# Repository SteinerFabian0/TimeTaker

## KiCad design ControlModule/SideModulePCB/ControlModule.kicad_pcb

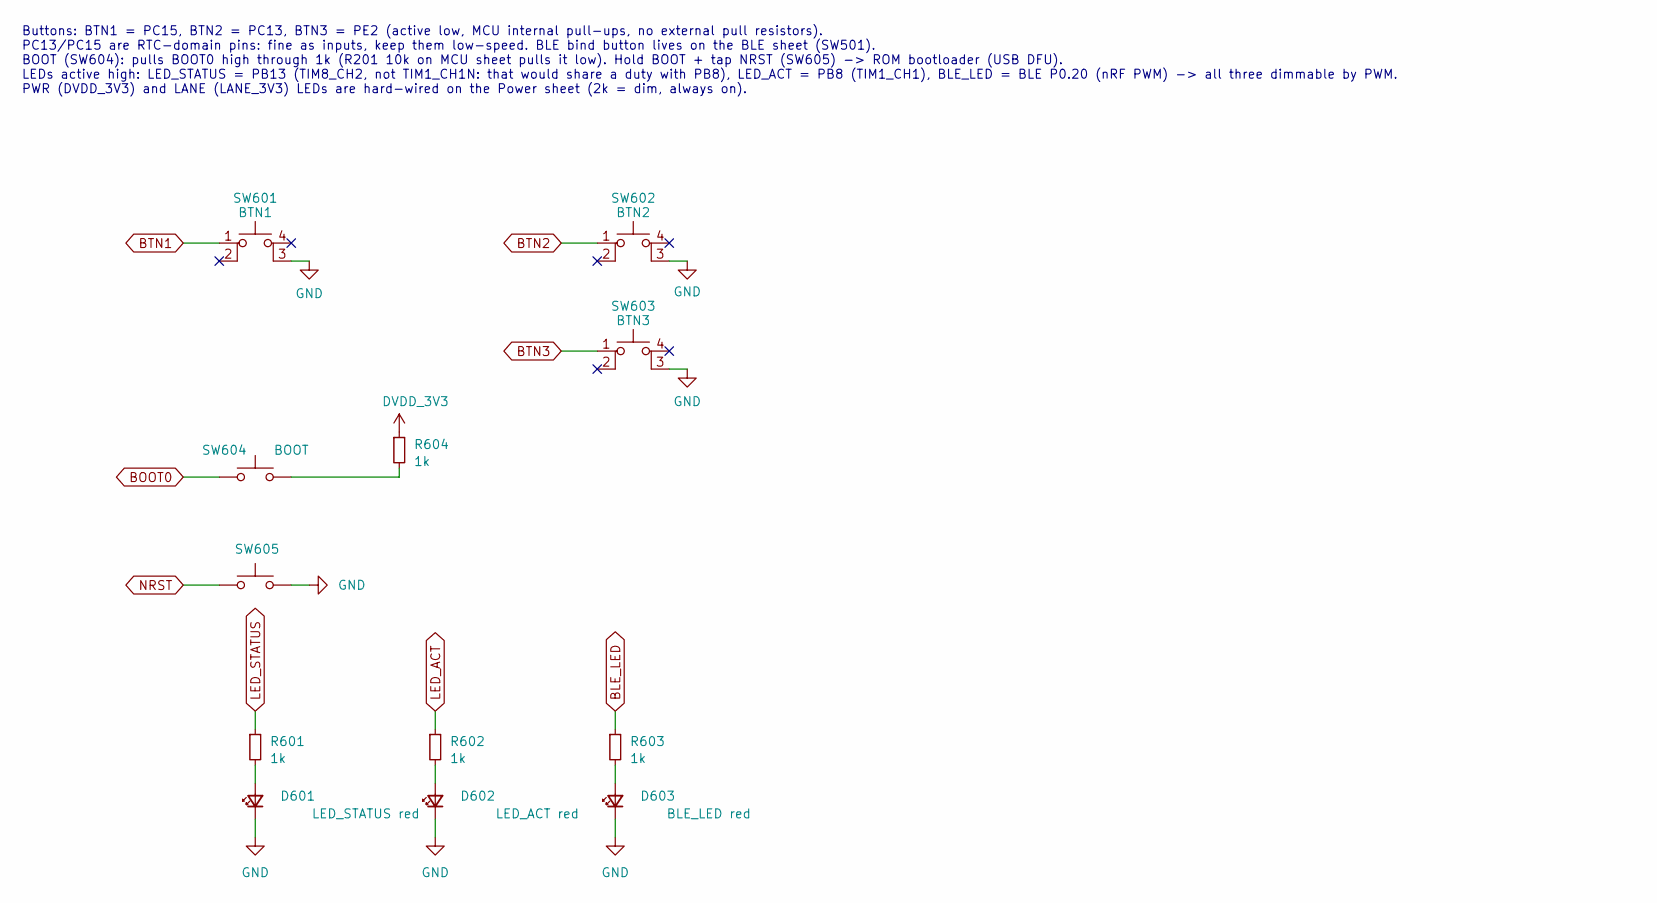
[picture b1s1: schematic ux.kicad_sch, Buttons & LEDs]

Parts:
D601: LED_STATUS red; LED_D5.0mm
D602: LED_ACT red; LED_D5.0mm
D603: BLE_LED red; LED_D5.0mm
R601, R602, R603, R604: 1k; R_0603_1608Metric
SW601: BTN1; Switch_Tactile_Smd_Gullwing
SW602: BTN2; Switch_Tactile_Smd_Gullwing
SW603: BTN3; Switch_Tactile_Smd_Gullwing
SW604: BOOT; SW_SPST_TS-1088-xR025; MPN TS-1088-AR02016; LCSC C720477
SW605: NRST; SW_SPST_TS-1088-xR025; MPN TS-1088-AR02016; LCSC C720477

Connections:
BLE_LED: R603.1; also elsewhere on the board
BOOT0: SW604.1; also elsewhere on the board
BTN1: SW601.1; also elsewhere on the board
BTN2: SW602.1; also elsewhere on the board
BTN3: SW603.1; also elsewhere on the board
DVDD_3V3: R604.1; also elsewhere on the board
GND: D601.1 (K), D602.1 (K), D603.1 (K), SW601.3 (K), SW602.3 (K), SW603.3 (K), SW605.2; also elsewhere on the board
LED_ACT: R602.1; also elsewhere on the board
LED_STATUS: R601.1; also elsewhere on the board
NRST: SW605.1; also elsewhere on the board
unnamed: D601.2 (A), R601.2
unnamed: D602.2 (A), R602.2
unnamed: D603.2 (A), R603.2
unnamed: R604.2, SW604.2

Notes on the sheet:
Buttons: BTN1 = PC15, BTN2 = PC13, BTN3 = PE2 (active low, MCU internal pull-ups, no external pull resistors). PC13/PC15 are RTC-domain pins: fine as inputs, keep them low-speed. BLE bind button lives on the BLE sheet (SW501). BOOT (SW604): pulls BOOT0 high through 1k (R201 10k on MCU sheet pulls i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

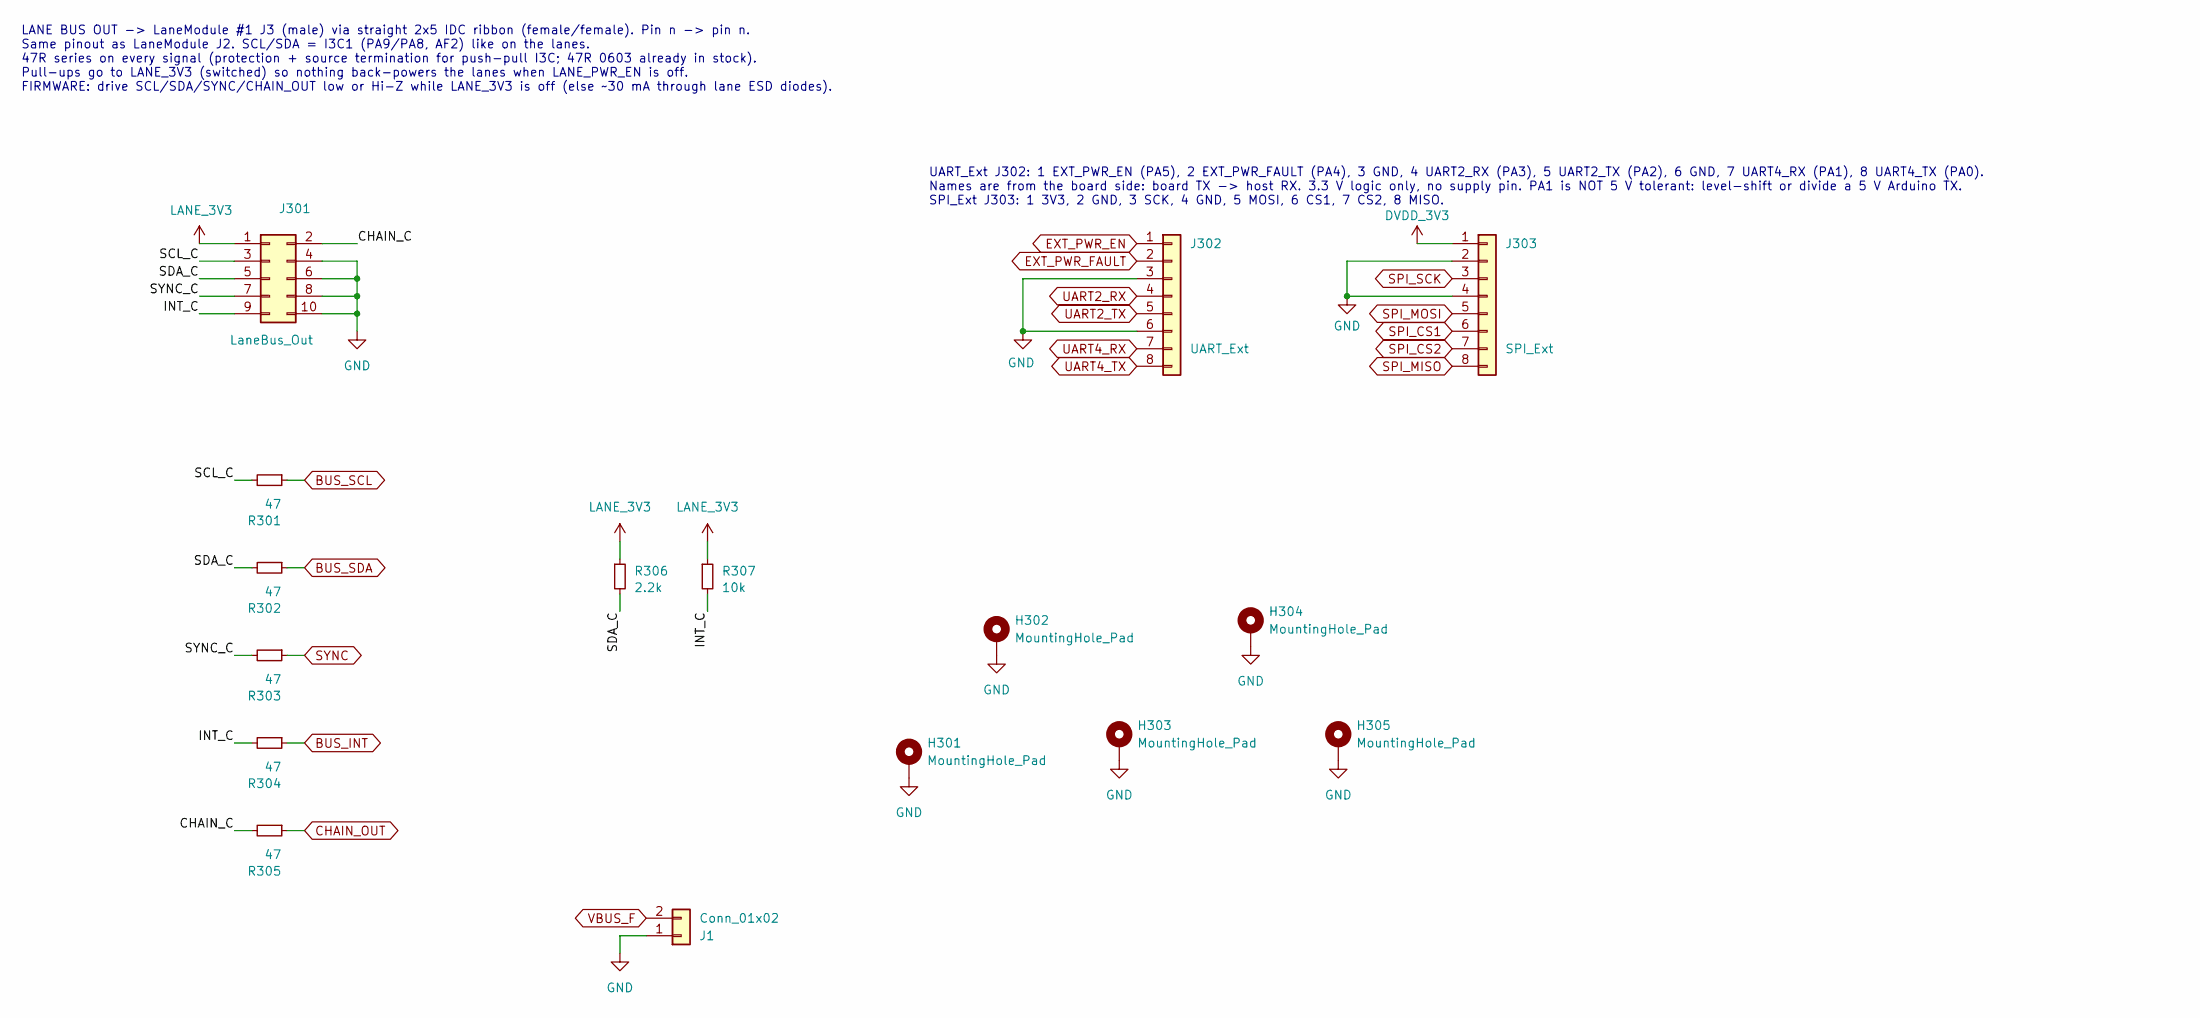
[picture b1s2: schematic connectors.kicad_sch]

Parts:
H301: MountingHole_Pad; MountingHole_3.2mm_M3_DIN965_Pad
H302, H303, H304, H305: MountingHole_Pad; MountingHole_2.5mm_Pad
J1: Conn_01x02; PinHeader_1x02_P2.54mm_Vertical
J301: LaneBus_Out; PinHeader_2x05_P2.54mm_Vertical
J302: UART_Ext; PinHeader_1x08_P2.54mm_Vertical
J303: SPI_Ext; PinHeader_1x08_P2.54mm_Vertical
R301, R302, R303, R304, R305: 47; R_0603_1608Metric; MPN 0603WAF470JT5E; LCSC C23182
R306: 2.2k; R_0603_1608Metric
R307: 10k; R_0603_1608Metric

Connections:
/Connectors/CHAIN_C: J301.2, R305.2
/Connectors/INT_C: J301.9, R304.2, R307.2
/Connectors/SCL_C: J301.3, R301.2
/Connectors/SDA_C: J301.5, R302.2, R306.2
/Connectors/SYNC_C: J301.7, R303.2
BUS_INT: R304.1; also elsewhere on the board
BUS_SCL: R301.1; also elsewhere on the board
BUS_SDA: R302.1; also elsewhere on the board
CHAIN_OUT: R305.1; also elsewhere on the board
DVDD_3V3: J303.1; also elsewhere on the board
EXT_PWR_EN: J302.1; also elsewhere on the board
EXT_PWR_FAULT: J302.2; also elsewhere on the board
GND: H301.1 (1_1), H302.1 (1_1), H303.1 (1_1), H304.1 (1_1), H305.1 (1_1), J1.1, J301.4, J301.6, J301.8, J301.10, J302.3, J302.6, J303.2, J303.4; also elsewhere on the board
LANE_3V3: J301.1, R306.1, R307.1; also elsewhere on the board
SPI_CS1: J303.6; also elsewhere on the board
SPI_CS2: J303.7; also elsewhere on the board
SPI_MISO: J303.8; also elsewhere on the board
SPI_MOSI: J303.5; also elsewhere on the board
SPI_SCK: J303.3; also elsewhere on the board
SYNC: R303.1; also elsewhere on the board
UART2_RX: J302.4; also elsewhere on the board
UART2_TX: J302.5; also elsewhere on the board
UART4_RX: J302.7; also elsewhere on the board
UART4_TX: J302.8; also elsewhere on the board
VBUS_F: J1.2; also elsewhere on the board

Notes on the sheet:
LANE BUS OUT -> LaneModule #1 J3 (male) via straight 2x5 IDC ribbon (female/female). Pin n -> pin n. Same pinout as LaneModule J2. SCL/SDA = I3C1 (PA9/PA8, AF2) like on the lanes. 47R series on every signal (protection + source termination for push-pull I3C; 47R 0603 already in stock). Pull-ups go 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
UART_Ext J302: 1 EXT_PWR_EN (PA5), 2 EXT_PWR_FAULT (PA4), 3 GND, 4 UART2_RX (PA3), 5 UART2_TX (PA2), 6 GND, 7 UART4_RX (PA1), 8 UART4_TX (PA0). Names are from the board side: board TX -> host RX. 3.3 V logic only, no supply pin. PA1 is NOT 5 V tolerant: level-shift or divide a 5 V Arduino TX. SPI_E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

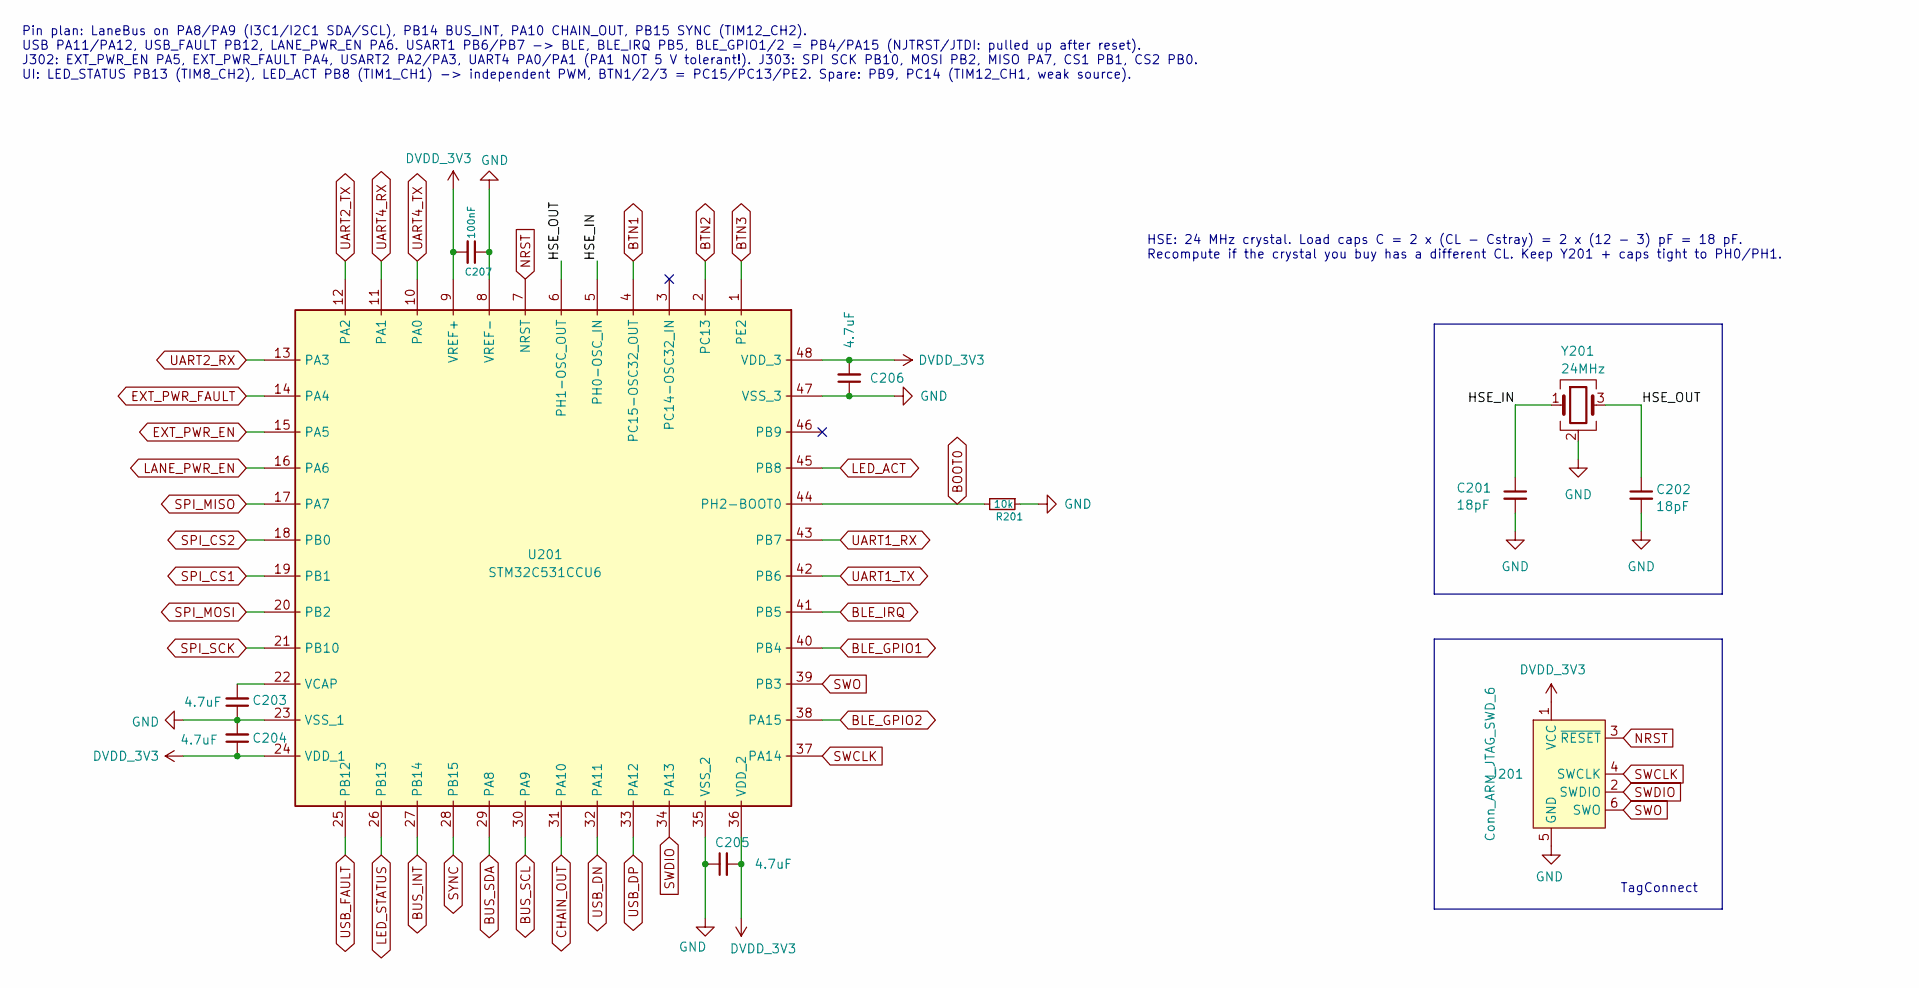
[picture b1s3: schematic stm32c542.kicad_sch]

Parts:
C201, C202: 18pF; C_0402_1005Metric
C203, C204, C205, C206: 4.7uF; C_0402_1005Metric; MPN CL05A475MP5NRNC; LCSC C23733
C207: 100nF; C_0402_1005Metric; MPN CL05B104KO5NNNC; LCSC C1525
J201: Conn_ARM_JTAG_SWD_6; Tag-Connect_TC2030-IDC-NL_2x03_P1.27mm_Vertical
R201: 10k; R_0603_1608Metric
U201: STM32C531CCU6; QFN50P700X700X60-49N-D; Manufacturer_Part_Number STM32C531CCU6
Y201: 24MHz; Crystal_SMD_3225-4Pin_3.2x2.5mm

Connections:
/STM32C5/HSE_IN: C201.1, U201.5 (PH0-OSC_IN), Y201.1
/STM32C5/HSE_OUT: C202.1, U201.6 (PH1-OSC_OUT), Y201.3
BLE_GPIO1: U201.40 (PB4); also elsewhere on the board
BLE_GPIO2: U201.38 (PA15); also elsewhere on the board
BLE_IRQ: U201.41 (PB5); also elsewhere on the board
BOOT0: R201.2, U201.44 (PH2-BOOT0); also elsewhere on the board
BTN1: U201.4 (PC15-OSC32_OUT); also elsewhere on the board
BTN2: U201.2 (PC13); also elsewhere on the board
BTN3: U201.1 (PE2); also elsewhere on the board
BUS_INT: U201.27 (PB14); also elsewhere on the board
BUS_SCL: U201.30 (PA9); also elsewhere on the board
BUS_SDA: U201.29 (PA8); also elsewhere on the board
CHAIN_OUT: U201.31 (PA10); also elsewhere on the board
DVDD_3V3: C204.1, C205.2, C206.2, C207.2, J201.1 (VCC), U201.9 (VREF+), U201.24 (VDD_1), U201.36 (VDD_2), U201.48 (VDD_3); also elsewhere on the board
EXT_PWR_EN: U201.15 (PA5); also elsewhere on the board
EXT_PWR_FAULT: U201.14 (PA4); also elsewhere on the board
GND: C201.2, C202.2, C203.1, C204.2, C205.1, C206.1, C207.1, J201.5 (GND), R201.1, U201.8 (VREF-), U201.23 (VSS_1), U201.35 (VSS_2), U201.47 (VSS_3), U201.49 (VSS_4), Y201.2 (G), Y201.4 (G); also elsewhere on the board
LANE_PWR_EN: U201.16 (PA6); also elsewhere on the board
LED_ACT: U201.45 (PB8); also elsewhere on the board
LED_STATUS: U201.26 (PB13); also elsewhere on the board
NRST: J201.3 (~RESET), U201.7 (NRST); also elsewhere on the board
unnamed: C203.2, U201.22 (VCAP)
SPI_CS1: U201.19 (PB1); also elsewhere on the board
SPI_CS2: U201.18 (PB0); also elsewhere on the board
SPI_MISO: U201.17 (PA7); also elsewhere on the board
SPI_MOSI: U201.20 (PB2); also elsewhere on the board
SPI_SCK: U201.21 (PB10); also elsewhere on the board
SWCLK: J201.4 (SWCLK), U201.37 (PA14)
SWDIO: J201.2 (SWDIO), U201.34 (PA13)
SWO: J201.6 (SWO), U201.39 (PB3)
SYNC: U201.28 (PB15); also elsewhere on the board
UART1_RX: U201.43 (PB7); also elsewhere on the board
UART1_TX: U201.42 (PB6); also elsewhere on the board
UART2_RX: U201.13 (PA3); also elsewhere on the board
UART2_TX: U201.12 (PA2); also elsewhere on the board
UART4_RX: U201.11 (PA1); also elsewhere on the board
UART4_TX: U201.10 (PA0); also elsewhere on the board
USB_DN: U201.32 (PA11); also elsewhere on the board
USB_DP: U201.33 (PA12); also elsewhere on the board
USB_FAULT: U201.25 (PB12); also elsewhere on the board

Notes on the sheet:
HSE: 24 MHz crystal. Load caps C = 2 x (CL - Cstray) = 2 x (12 - 3) pF = 18 pF. Recompute if the crystal you buy has a different CL. Keep Y201 + caps tight to PH0/PH1.
Pin plan: LaneBus on PA8/PA9 (I3C1/I2C1 SDA/SCL), PB14 BUS_INT, PA10 CHAIN_OUT, PB15 SYNC (TIM12_CH2). USB PA11/PA12, USB_FAULT PB12, LANE_PWR_EN PA6. USART1 PB6/PB7 -> BLE, BLE_IRQ PB5, BLE_GPIO1/2 = PB4/PA15 (NJTRST/JTDI: pulled up after reset). J302: EXT_PWR_EN PA5, EXT_PWR_FAULT PA4, USART2 PA2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
TagConnect

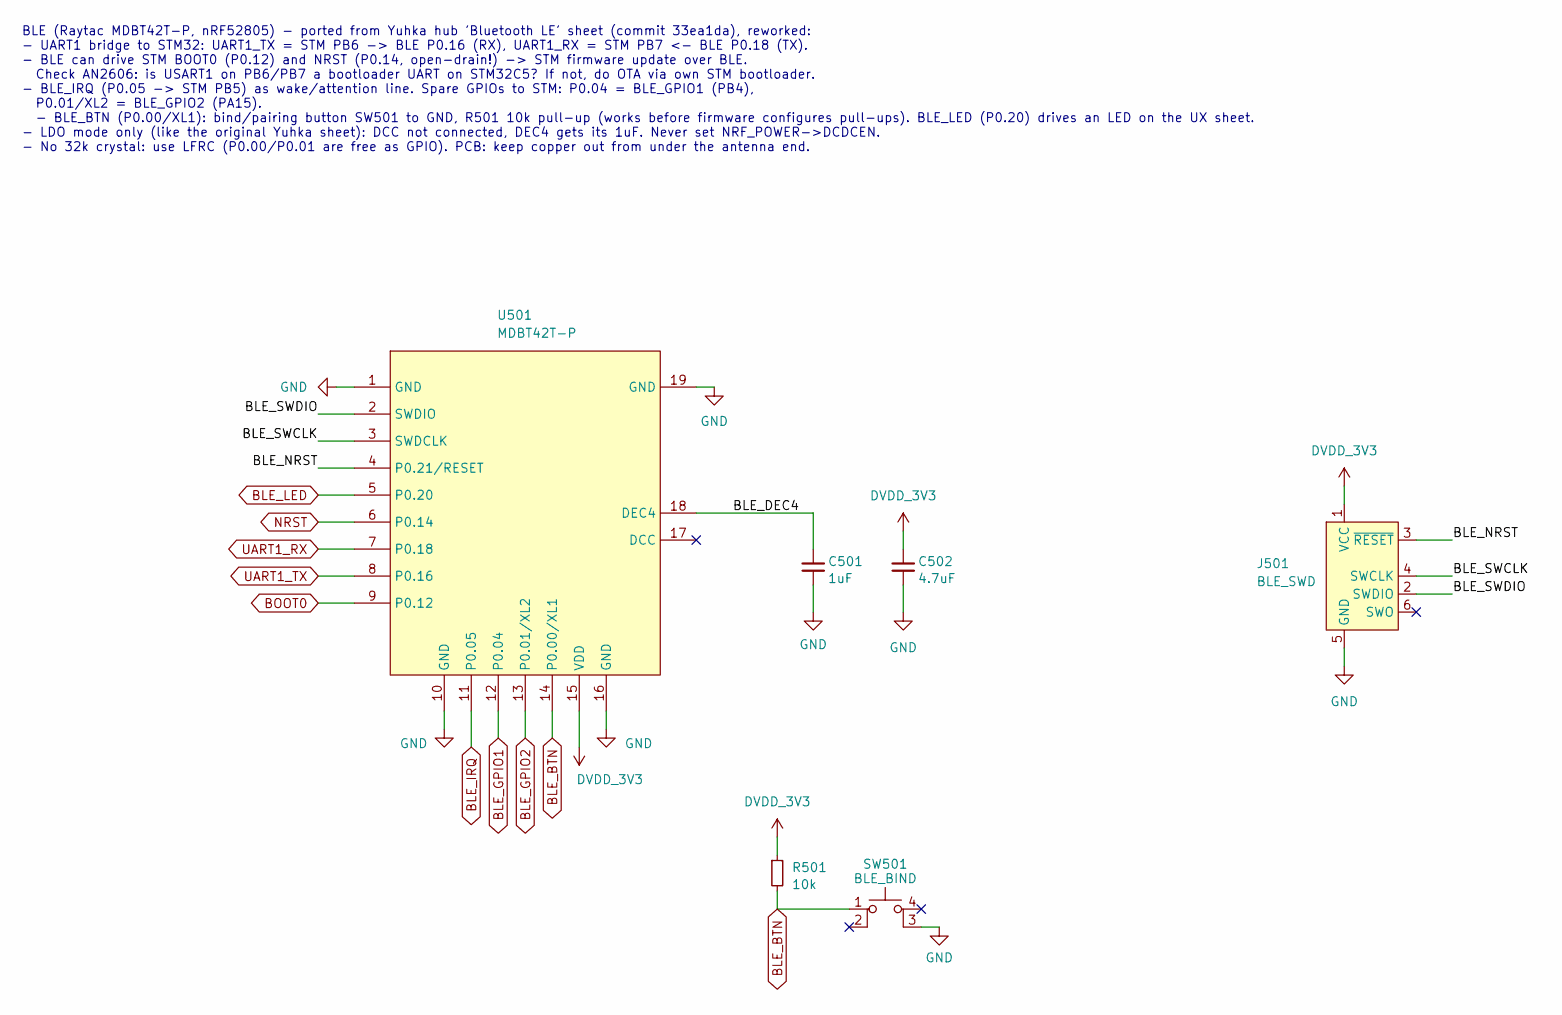
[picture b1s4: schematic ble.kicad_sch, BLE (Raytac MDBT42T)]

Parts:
C501: 1uF; C_0402_1005Metric
C502: 4.7uF; C_0402_1005Metric; MPN CL05A475MP5NRNC; LCSC C23733
J501: BLE_SWD; Tag-Connect_TC2030-IDC-NL_2x03_P1.27mm_Vertical
R501: 10k; R_0603_1608Metric
SW501: BLE_BIND; Switch_Tactile_Smd_Gullwing
U501: MDBT42T-P; MDBT42T

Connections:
/BLE/BLE_DEC4: C501.1, U501.18 (DEC4)
/BLE/BLE_NRST: J501.3 (~RESET), U501.4 (P0.21/RESET)
/BLE/BLE_SWCLK: J501.4 (SWCLK), U501.3 (SWDCLK)
/BLE/BLE_SWDIO: J501.2 (SWDIO), U501.2 (SWDIO)
BLE_BTN: R501.2, SW501.1, U501.14 (P0.00/XL1)
BLE_GPIO1: U501.12 (P0.04); also elsewhere on the board
BLE_GPIO2: U501.13 (P0.01/XL2); also elsewhere on the board
BLE_IRQ: U501.11 (P0.05); also elsewhere on the board
BLE_LED: U501.5 (P0.20); also elsewhere on the board
BOOT0: U501.9 (P0.12); also elsewhere on the board
DVDD_3V3: C502.1, J501.1 (VCC), R501.1, U501.15 (VDD); also elsewhere on the board
GND: C501.2, C502.2, J501.5 (GND), SW501.3 (K), U501.1 (GND), U501.10 (GND), U501.16 (GND), U501.19 (GND); also elsewhere on the board
NRST: U501.6 (P0.14); also elsewhere on the board
UART1_RX: U501.7 (P0.18); also elsewhere on the board
UART1_TX: U501.8 (P0.16); also elsewhere on the board

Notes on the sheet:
BLE (Raytac MDBT42T-P, nRF52805) - ported from Yuhka hub 'Bluetooth LE' sheet (commit 33ea1da), reworked: - UART1 bridge to STM32: UART1_TX = STM PB6 -> BLE P0.16 (RX), UART1_RX = STM PB7 <- BLE P0.18 (TX). - BLE can drive STM BOOT0 (P0.12) and NRST (P0.14, open-drain!) -> STM firmware update over 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

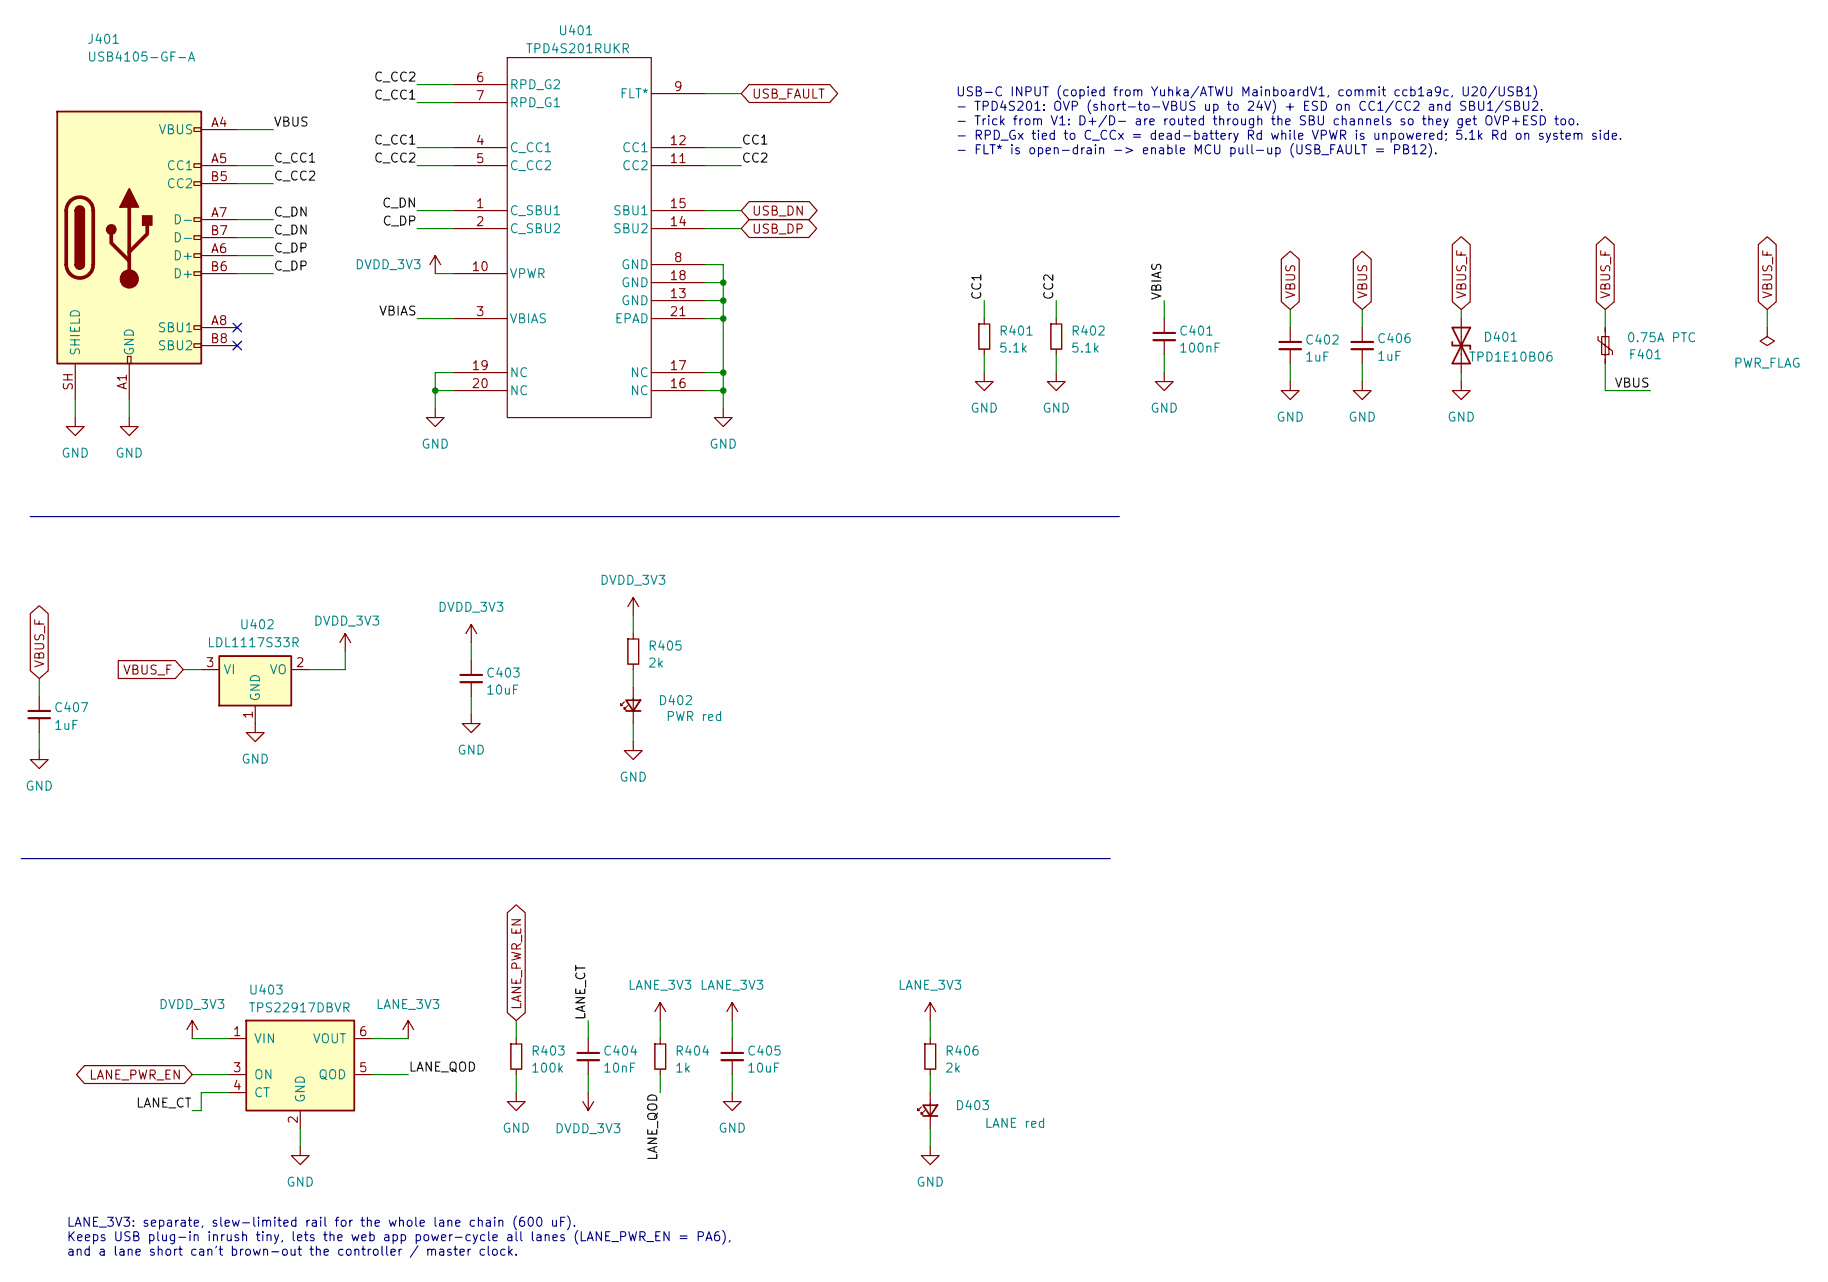
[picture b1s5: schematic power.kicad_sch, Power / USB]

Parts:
C401: 100nF; C_0402_1005Metric; MPN CL05B104KO5NNNC; LCSC C1525
C402, C406, C407: 1uF; C_0603_1608Metric; Voltage 50V; MPN CL10A105KB8NNNC; LCSC C15849
C403, C405: 10uF; C_0603_1608Metric; MPN CL10A106KP8NNNC; LCSC C19702
C404: 10nF; C_0402_1005Metric
D401: TPD1E10B06; Texas_DPY0002A_0.6x1mm_P0.65mm; MPN TPD1E10B06DPYR; LCSC C1847652
D402: PWR red; LED_D5.0mm
D403: LANE red; LED_D5.0mm
F401: 0.75A PTC; Fuse_1206_3216Metric; MPN 1206L075THYR
J401: USB4105-GF-A; USB_C_Receptacle_GCT_USB4105-xx-A_16P_TopMnt_Horizontal
R401, R402: 5.1k; R_0402_1005Metric
R403: 100k; R_0603_1608Metric
R404: 1k; R_0603_1608Metric
R405, R406: 2k; R_0603_1608Metric
U401: TPD4S201RUKR; QFN_TPD4S201RUKR_TEX
U402: LDL1117S33R; SOT-223-3_TabPin2
U403: TPS22917DBVR; SOT-23-6

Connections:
/Power/CC1: R401.1, U401.12 (CC1)
/Power/CC2: R402.1, U401.11 (CC2)
/Power/C_CC1: J401.A5 (CC1), U401.4 (C_CC1), U401.7 (RPD_G1)
/Power/C_CC2: J401.B5 (CC2), U401.5 (C_CC2), U401.6 (RPD_G2)
/Power/C_DN: J401.A7 (D-), J401.B7 (D-), U401.1 (C_SBU1)
/Power/C_DP: J401.A6 (D+), J401.B6 (D+), U401.2 (C_SBU2)
/Power/LANE_CT: C404.1, U403.4 (CT)
/Power/LANE_QOD: R404.2, U403.5 (QOD)
/Power/VBIAS: C401.1, U401.3 (VBIAS)
DVDD_3V3: C403.1, C404.2, R405.1, U401.10 (VPWR), U402.2 (VO), U403.1 (VIN); also elsewhere on the board
GND: C401.2, C402.2, C403.2, C405.2, C406.2, C407.2, D401.2 (A2), D402.1 (K), D403.1 (K), J401.A1 (GND), J401.A12 (GND), J401.B1 (GND), J401.B12 (GND), J401.SH (SHIELD), R401.2, R402.2, R403.2, U401.8 (GND), U401.13 (GND), U401.16 (NC), U401.17 (NC), U401.18 (GND), U401.19 (NC), U401.20 (NC), U401.21 (EPAD), U402.1 (GND), U403.2 (GND); also elsewhere on the board
LANE_3V3: C405.1, R404.1, R406.1, U403.6 (VOUT); also elsewhere on the board
LANE_PWR_EN: R403.1, U403.3 (ON); also elsewhere on the board
unnamed: D402.2 (A), R405.2
unnamed: D403.2 (A), R406.2
USB_DN: U401.15 (SBU1); also elsewhere on the board
USB_DP: U401.14 (SBU2); also elsewhere on the board
USB_FAULT: U401.9 (FLT*); also elsewhere on the board
VBUS: C402.1, C406.1, F401.1, J401.A4 (VBUS), J401.A9 (VBUS), J401.B4 (VBUS), J401.B9 (VBUS)
VBUS_F: C407.1, D401.1 (A1), F401.2, U402.3 (VI); also elsewhere on the board

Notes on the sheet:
USB-C INPUT (copied from Yuhka/ATWU MainboardV1, commit ccb1a9c, U20/USB1) - TPD4S201: OVP (short-to-VBUS up to 24V) + ESD on CC1/CC2 and SBU1/SBU2. - Trick from V1: D+/D- are routed through the SBU channels so they get OVP+ESD too. - RPD_Gx tied to C_CCx = dead-battery Rd while VPWR is unpowered; 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
LANE_3V3: separate, slew-limited rail for the whole lane chain (600 uF). Keeps USB plug-in inrush tiny, lets the web app power-cycle all lanes (LANE_PWR_EN = PA6), and a lane short can't brown-out the controller / master clock.

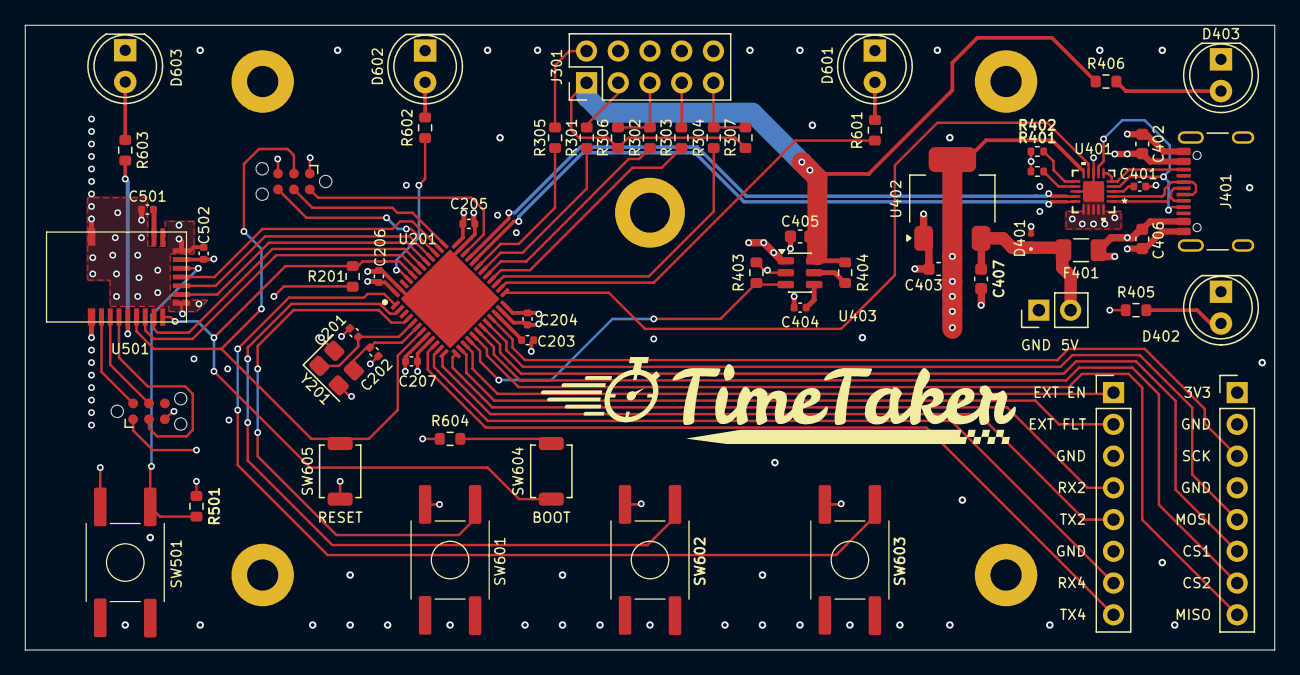
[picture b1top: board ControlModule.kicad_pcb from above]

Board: 4 copper layers, 100.0 x 50.0 mm, 66 parts (0 on the bottom side), 69 nets.

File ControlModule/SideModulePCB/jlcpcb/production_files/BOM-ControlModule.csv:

Comment,Designator,Footprint,LCSC,Quantity
100nF,"C207,C401",C_0402_1005Metric,C1525,2
10uF,"C403,C405",C_0603_1608Metric,C19702,2
1uF,"C402,C406,C407",C_0603_1608Metric,C15849,3
4.7uF,"C203,C204,C205,C206,C502",C_0402_1005Metric,C23733,5
47,"R301,R302,R303,R304,R305",R_0603_1608Metric,C23182,5
BOOT,SW604,SW_SPST_TS-1088-xR025,C720477,1
NRST,SW605,SW_SPST_TS-1088-xR025,C720477,1
TPD1E10B06,D401,Texas_DPY0002A_0.6x1mm_P0.65mm,C1847652,1
24MHz,Y201,Crystal_SMD_3225-4Pin_3.2x2.5mm,,1
PWR red,D402,LED_D5.0mm,,1
BTN2,SW602,Switch_Tactile_Smd_Gullwing,,1
LaneBus_Out,J301,PinHeader_2x05_P2.54mm_Vertical,,1
2k,R405,R_0603_1608Metric,,1
TPD4S201RUKR,U401,QFN_TPD4S201RUKR_TEX,,1
1k,R603,R_0603_1608Metric,,1
Conn_01x02,J1,PinHeader_1x02_P2.54mm_Vertical,,1
USB4105-GF-A,J401,USB_C_Receptacle_GCT_USB4105-xx-A_16P_TopMnt_Horizontal,,1
BTN1,SW601,Switch_Tactile_Smd_Gullwing,,1
LED_ACT red,D602,LED_D5.0mm,,1
STM32C531CCU6,U201,QFN50P700X700X60-49N-D,,1
TPS22917DBVR,U403,SOT-23-6,,1
SPI_Ext,J303,PinHeader_1x08_P2.54mm_Vertical,,1
1k,R601,R_0603_1608Metric,,1
1uF,C501,C_0402_1005Metric,,1
1k,R602,R_0603_1608Metric,,1
MDBT42T-P,U501,MDBT42T,,1
LANE red,D403,LED_D5.0mm,,1
BLE_SWD,J501,Tag-Connect_TC2030-IDC-NL_2x03_P1.27mm_Vertical,,1
0.75A PTC,F401,Fuse_1206_3216Metric,,1
2.2k,R306,R_0603_1608Metric,,1
18pF,C202,C_0402_1005Metric,,1
UART_Ext,J302,PinHeader_1x08_P2.54mm_Vertical,,1
LDL1117S33R,U402,SOT-223-3_TabPin2,,1
100k,R403,R_0603_1608Metric,,1
BTN3,SW603,Switch_Tactile_Smd_Gullwing,,1
18pF,C201,C_0402_1005Metric,,1
2k,R406,R_0603_1608Metric,,1
1k,R604,R_0603_1608Metric,,1
10nF,C404,C_0402_1005Metric,,1
BLE_LED red,D603,LED_D5.0mm,,1
BLE_BIND,SW501,Switch_Tactile_Smd_Gullwing,,1
10k,R307,R_0603_1608Metric,,1
5.1k,R401,R_0402_1005Metric,,1
5.1k,R402,R_0402_1005Metric,,1
1k,R404,R_0603_1608Metric,,1
10k,R201,R_0603_1608Metric,,1
10k,R501,R_0603_1608Metric,,1
LED_STATUS red,D601,LED_D5.0mm,,1

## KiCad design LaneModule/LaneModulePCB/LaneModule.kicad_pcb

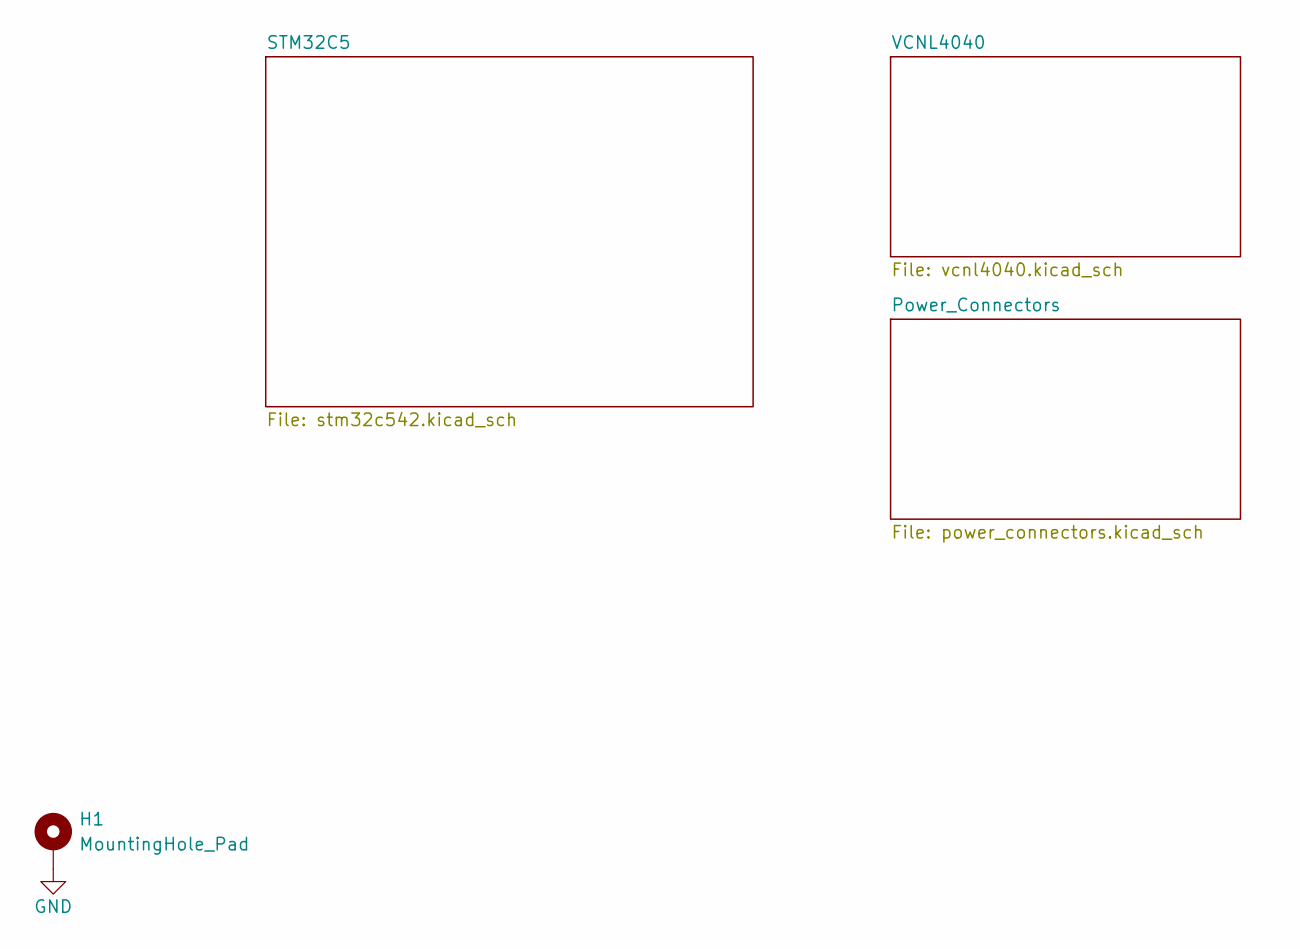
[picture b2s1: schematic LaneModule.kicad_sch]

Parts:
H1: MountingHole_Pad; MountingHole_2.5mm_Pad

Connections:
GND: H1.1 (1_1); also elsewhere on the board

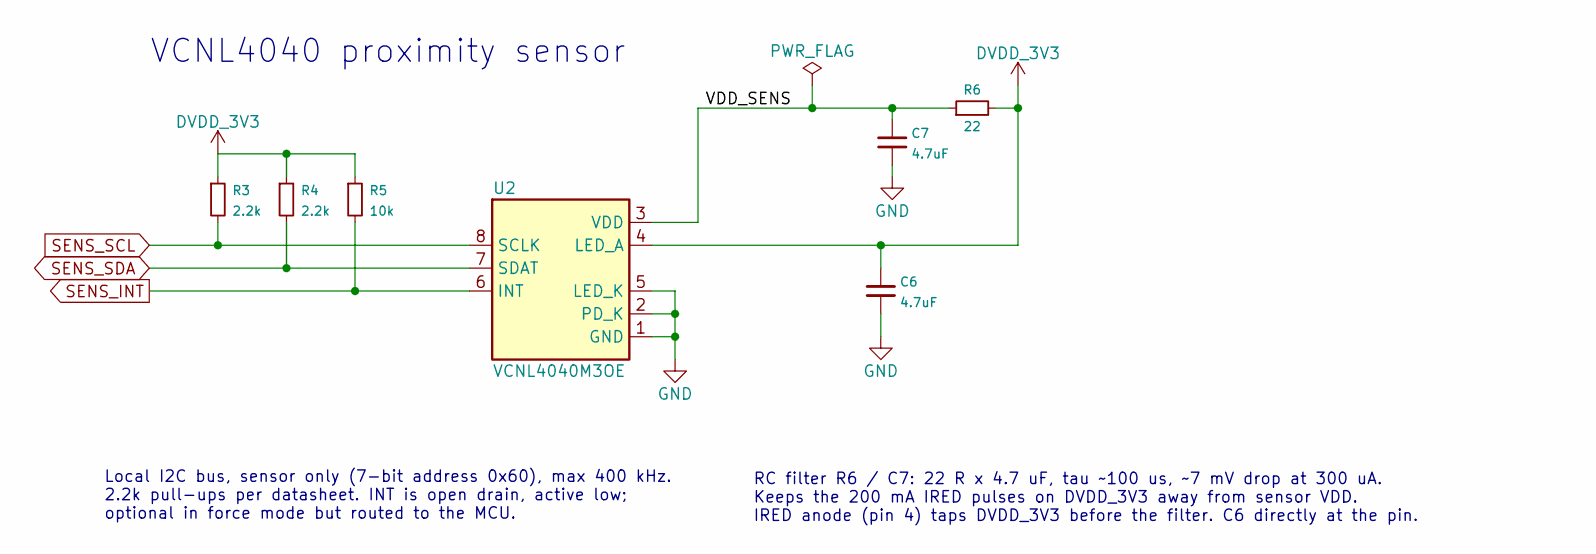
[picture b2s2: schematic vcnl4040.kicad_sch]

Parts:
C6, C7: 4.7uF; C_0402_1005Metric; MPN CL05A475MP5NRNC; LCSC C23733
R3, R4: 2.2k; R_0603_1608Metric
R5: 10k; R_0603_1608Metric
R6: 22; R_0603_1608Metric
U2: VCNL4040M3OE; MPN VCNL4040M3OE; LCSC C142526

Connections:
/VCNL4040/VDD_SENS: C7.1, R6.1, U2.3 (VDD)
DVDD_3V3: C6.1, R3.1, R4.1, R5.1, R6.2, U2.4 (LED_A); also elsewhere on the board
GND: C6.2, C7.2, U2.1 (GND), U2.2 (PD_K), U2.5 (LED_K); also elsewhere on the board
SENS_INT: R5.2, U2.6 (INT); also elsewhere on the board
SENS_SCL: R3.2, U2.8 (SCLK); also elsewhere on the board
SENS_SDA: R4.2, U2.7 (SDAT); also elsewhere on the board

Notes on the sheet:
VCNL4040 proximity sensor
Local I2C bus, sensor only (7-bit address 0x60), max 400 kHz. 2.2k pull-ups per datasheet. INT is open drain, active low; optional in force mode but routed to the MCU.
RC filter R6 / C7: 22 R x 4.7 uF, tau ~100 us, ~7 mV drop at 300 uA. Keeps the 200 mA IRED pulses on DVDD_3V3 away from sensor VDD. IRED anode (pin 4) taps DVDD_3V3 before the filter. C6 directly at the pin.

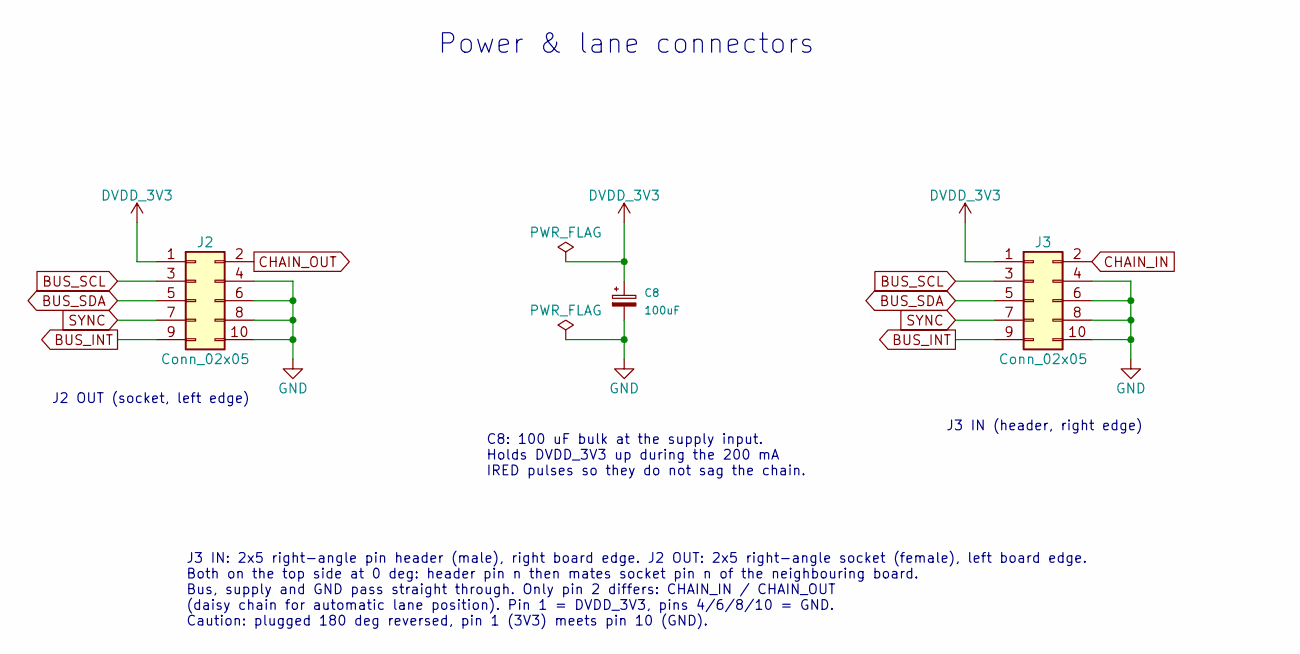
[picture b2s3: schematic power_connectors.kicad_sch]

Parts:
C8: 100uF; CP_Elec_5x5.4; MPN RVT1A101M0505; LCSC C72473
J2: Conn_02x05; PinSocket_2x05_P2.54mm_Horizontal
J3: Conn_02x05; PinHeader_2x05_P2.54mm_Horizontal

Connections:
BUS_INT: J2.9, J3.9; also elsewhere on the board
BUS_SCL: J2.3, J3.3; also elsewhere on the board
BUS_SDA: J2.5, J3.5; also elsewhere on the board
CHAIN_IN: J3.2; also elsewhere on the board
CHAIN_OUT: J2.2; also elsewhere on the board
DVDD_3V3: C8.1, J2.1, J3.1; also elsewhere on the board
GND: C8.2, J2.4, J2.6, J2.8, J2.10, J3.4, J3.6, J3.8, J3.10; also elsewhere on the board
SYNC: J2.7, J3.7; also elsewhere on the board

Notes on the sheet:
J3 IN (header, right edge)
J2 OUT (socket, left edge)
J3 IN: 2x5 right-angle pin header (male), right board edge. J2 OUT: 2x5 right-angle socket (female), left board edge. Both on the top side at 0 deg: header pin n then mates socket pin n of the neighbouring board. Bus, supply and GND pass straight through. Only pin 2 differs: CHAIN_IN / CHAIN_OUT (d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
Power & lane connectors
C8: 100 uF bulk at the supply input. Holds DVDD_3V3 up during the 200 mA IRED pulses so they do not sag the chain.
